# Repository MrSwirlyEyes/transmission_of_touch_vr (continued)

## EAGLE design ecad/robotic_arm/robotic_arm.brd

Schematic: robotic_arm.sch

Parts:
A6: 2.45GHz; ANTC6522X100
AVR_ISP: AVR ISP; HDRV6W64P254_2X3_762X508X838B
B1: 50/100; RESCAXE65P200X125X95-6
C1, C2, C3, C4, C5, C6, C7, C10, C12, C14, C16, C19, C22, C24, C26, C28, C30, C47, C48, C49, C50, C51, C52, C53, C54, C63, C79, C83, C85, C93, C96, C98: 0.1uF/50V; CAPC1005X55_SMD-0402
C8, C29, C92: 10uF/6.3V; CAPC1005X55_SMD-0402
C9, C11, C13, C15, C17: 100uF/25V; CAPPRD200W50D500H1100B
C20, C27, C80: 1000uF/16V; CAPPRD350W60D800H2000B
C21, C23, C55, C57, C58: 1uF/25V; CAPC1005X55_SMD-0402
C59, C60: 12pF/100V; CAPC1005X55_SMD-0402
C61: 22pF/100V/0402; CAPC1005X55_SMD-0402
C62: 0.75pF/50V; CAPC1005X55_SMD-0402
C94, C95, C97: 10uF/25V; CAPC2012X95_SMD-0805
D1: 150mA/75V; DFN100X60X55-2
D2, D7: 1A/50V; SODFL3516X170
DEMUX1: CH16_MUX-DEMUX; SOP65P780X200-24
FSR_INDEX: 10K; _MOLEX-0530470210_VERT_PITCH-1.25MM
FSR_MIDDLE: 10K; _MOLEX-0530470210_VERT_PITCH-1.25MM
FSR_PALM: 10K; _MOLEX-0530470210_VERT_PITCH-1.25MM
FSR_PINKY: 10K; _MOLEX-0530470210_VERT_PITCH-1.25MM
FSR_RING: 10K; _MOLEX-0530470210_VERT_PITCH-1.25MM
FSR_THUMB: 10K; _MOLEX-0530470210_VERT_PITCH-1.25MM
J1: 5A/28V; POWER_JACK_PTH_ID2.1MM-OD5.5MM
JP1: PTH RA VERT MALE; HDRRA6W64P254_1X6_1524X254X254B_FTDI
JP3: JUMPER_SMD_3-PAD_NO_SILK; SMT-JUMPER_3_NO_SILK
L1, L2: 10uH/380mA; INDC1608X60-0603
LED1: BLUE; LEDC1005X40_LED-0402
LIPO1: LIPO 2S; 1X02_WIRE_CONNECTOR_AWG-18
MCU: ATMEGA128RFA1; QFN50P900X900X90-64
NOISE_BR, NOISE_BR1: NET_BRIDGE
PWM_DRIVER: PCA9685; SOP65P650X110-28
R1, R10, R16, R39, R40, R41, R42, R43: 10K; RESC1005X35_SMD-0402
R2, R3: 1K; RESC1005X35_SMD-0402
R17, R18: 4.7K; RESC1005X35_SMD-0402
RX_LED: RED; LEDC1005X40_LED-0402
SERVO_INDEX: HK15298B; HDRV3W64P254_1X3_762X254X838B
SERVO_MIDDLE: HK15298B; HDRV3W64P254_1X3_762X254X838B
SERVO_PINKY: HK15298B; HDRV3W64P254_1X3_762X254X838B
SERVO_RING: HK15298B; HDRV3W64P254_1X3_762X254X838B
SERVO_THUMB: HK15298B; HDRV3W64P254_1X3_762X254X838B
SW1: 5A/28V; SW_TOGGLE_SPDT_5A-28V_13L-7W
TEMP_INDEX: TMP36; _MOLEX-0530470310_VERT_PITCH-1.25MM
TEMP_MIDDLE: TMP36; _MOLEX-0530470310_VERT_PITCH-1.25MM
TEMP_PINKY: TMP36; _MOLEX-0530470310_VERT_PITCH-1.25MM
TEMP_RING: TMP36; _MOLEX-0530470310_VERT_PITCH-1.25MM
TEMP_THUMB: TMP36; _MOLEX-0530470310_VERT_PITCH-1.25MM
TX_LED: GREEN; LEDC1005X40_LED-0402
VREG-ANALOG: MCP1700-1802 1.8V/200mA; SOT95P237X112-3_SOT-23-3
VREG-MCU: TPS76833QDR 1A/3.3V; SOIC127P600X265-8
VREG-SERVOS: MIC29501-5.0 5A/5V; TO170P1363X457-6
Y1: 16 MHz; OSCCC500X320X110_CRYSTAL

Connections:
3.3V: C19.1, C24.1, C52.1, C53.1, C54.1, C55.1, C58.1, C63.1, C92.1, C93.1, D1.K, D2.A, L1.1, MCU.23 (DEVDD), MCU.34 (DEVDD), MCU.44 (DEVDD), MCU.54 (DEVDD), PWM_DRIVER.28 (VCC), R17.2, R18.2, R43.2, VREG-MCU.5 (VOUT), VREG-MCU.6 (VOUT)
5V: C1.1, C9.A, C10.1, C11.A, C12.1, C13.A, C14.1, C15.A, C16.1, C17.A, C20.A, C83.1, C94.1, D7.A, SERVO_INDEX.VCC, SERVO_MIDDLE.VCC, SERVO_PINKY.VCC, SERVO_RING.VCC, SERVO_THUMB.VCC, VREG-SERVOS.4 (VOUT)
+: J1.PWR, LIPO1.+, SW1.S1
-: J1.GND_BATTERY, LIPO1.-
A1.8V: C28.1, C29.1, JP3.1, MCU.62 (AREF), VREG-ANALOG.2 (VO)
A3.3V: C2.1, C3.1, C4.1, C5.1, C6.1, C7.1, C8.1, C22.1, C23.1, C26.1, C85.1, DEMUX1.24 (VCC), JP3.3, L1.2, MCU.59 (EVDD), TEMP_INDEX.VCC, TEMP_MIDDLE.VCC, TEMP_PINKY.VCC, TEMP_RING.VCC, TEMP_THUMB.VCC, VREG-ANALOG.3 (VI)
AGND: B1.5 (GND), C2.2, C3.2, C4.2, C5.2, C6.2, C7.2, C8.2, C22.2, C23.2, C24.2, C26.2, C28.2, C29.2, C30.2, C47.2, C48.2, C49.2, C50.2, C51.2, C61.2, C62.2, C85.2, DEMUX1.2 (C7), DEMUX1.3 (C6), DEMUX1.12 (GND), DEMUX1.15 (!EN), DEMUX1.21 (C10), DEMUX1.22 (C9), DEMUX1.23 (C8), L2.2, MCU.7 (AVSS_RFP), MCU.10 (AVSS_RFN), MCU.58 (AVSS), MCU.61 (AVSS), MCU.EP (AVSS), MCU.P$1 (AVSS), MCU.P$2 (AVSS), MCU.P$3 (AVSS), MCU.P$4 (AVSS), MCU.P$5 (AVSS), R10.1, R16.1, R39.1, R40.1, R41.1, R42.1, TEMP_INDEX.GND, TEMP_MIDDLE.GND, TEMP_PINKY.GND, TEMP_RING.GND, TEMP_THUMB.GND, VREG-ANALOG.1 (GND)
FSR_INDEX: DEMUX1.8 (C1), FSR_INDEX.2 (-), R39.2
FSR_MIDDLE: DEMUX1.7 (C2), FSR_MIDDLE.2 (-), R40.2
FSR_PALM: DEMUX1.4 (C5), FSR_PALM.2 (-), R10.2
FSR_PINKY: DEMUX1.5 (C4), FSR_PINKY.2 (-), R42.2
FSR_RING: DEMUX1.6 (C3), FSR_RING.2 (-), R41.2
FSR_THUMB: DEMUX1.9 (C0), FSR_THUMB.2 (-), R16.2
GND: AVR_ISP.GND, C19.2, C21.2, C27.K, C52.2, C53.2, C54.2, C55.2, C57.2, C58.2, C59.1, C60.1, C63.2, C80.K, C92.2, C93.2, C95.2, C96.2, J1.GND_JACK, JP1.GND, MCU.11 (TST), MCU.20 (DVSS), MCU.24 (DVSS), MCU.33 (CLKI), MCU.35 (DVSS), MCU.45 (DVSS), MCU.55 (DVSS), NOISE_BR.P$2, NOISE_BR1.P$1, PWM_DRIVER.1 (A0), PWM_DRIVER.2 (A1), PWM_DRIVER.3 (A2), PWM_DRIVER.4 (A3), PWM_DRIVER.5 (A4), PWM_DRIVER.14 (GND), PWM_DRIVER.23 (!OE), PWM_DRIVER.24 (A5), PWM_DRIVER.25 (EXTCLK), R1.1, R2.1, R3.1, VREG-MCU.1 (GND), VREG-MCU.2 (!EN)
MISO: AVR_ISP.MISO, MCU.39 ((PDO/PCINT3/MISO/D12)PB3)
MOSI: AVR_ISP.MOSI, MCU.38 ((PDI/PCINT2/MOSI/D11)PB2)
unnamed: L2.1, NOISE_BR1.P$2
unnamed: LED1.K, R1.2
unnamed: R3.2, TX_LED.K
unnamed: R2.2, RX_LED.K
unnamed: C21.1, MCU.21 (DVDD), MCU.22 (DVDD)
unnamed: C57.1, MCU.60 (AVDD)
unnamed: C60.2, MCU.57 (XTAL1), Y1.1 (XTAL1)
unnamed: B1.3 (OUT1), MCU.9 (RFN)
unnamed: B1.4 (OUT2), MCU.8 (RFP)
unnamed: B1.2 (GND), C61.1
unnamed: C59.2, MCU.56 (XTAL2), Y1.3 (XTAL2)
unnamed: A6.1, B1.1 (IN), C62.1
unnamed: C79.1, JP1.DTR
NGND: C1.2, C9.K, C10.2, C11.K, C12.2, C13.K, C14.2, C15.K, C16.2, C17.K, C20.K, C83.2, C94.2, C97.2, C98.2, NOISE_BR.P$1, SERVO_INDEX.GND, SERVO_MIDDLE.GND, SERVO_PINKY.GND, SERVO_RING.GND, SERVO_THUMB.GND, VREG-SERVOS.3 (GND), VREG-SERVOS.TAB (GND)
RESET: AVR_ISP.RESET, C79.2, D1.A, MCU.12 (RSTN), R43.1
RX: JP1.TXO, MCU.46 ((PCINT8/RXD0/D0)PE0)
RX_LED: MCU.42 ((PCINT6/OC1B/D34-PWM34)PB6), RX_LED.A
S0: DEMUX1.10 (S0), MCU.50 ((INT4/OC3B/D4-PWM4)PE4)
S1: DEMUX1.11 (S1), MCU.49 ((AIN1/OC3A/D3-PWM3)PE3)
S2: DEMUX1.14 (S2), MCU.52 ((T3/INT6/D6)PE6)
S3: DEMUX1.13 (S3), MCU.51 ((INT5/OC3C/D5-PWM5)PE5)
SCK: AVR_ISP.SCK, MCU.37 ((PCINT1/SCK/D13)PB1)
SCL: MCU.25 ((INT0/SCL/D15)PD0), PWM_DRIVER.26 (SCL), R17.1
SDA: MCU.26 ((INT1/SDA/D14)PD1), PWM_DRIVER.27 (SDA), R18.1
SERVO_INDEX: PWM_DRIVER.18 (PWM11), SERVO_INDEX.SIG
SERVO_MIDDLE: PWM_DRIVER.17 (PWM10), SERVO_MIDDLE.SIG
SERVO_PINKY: PWM_DRIVER.15 (PWM8), SERVO_PINKY.SIG
SERVO_RING: PWM_DRIVER.16 (PWM9), SERVO_RING.SIG
SERVO_THUMB: PWM_DRIVER.19 (PWM12), SERVO_THUMB.SIG
SIG: DEMUX1.1 (SIG), MCU.1 ((ADC2/DIG2/A2*)PF2)
TEMP_INDEX: DEMUX1.17 (C14), TEMP_INDEX.SIG
TEMP_MIDDLE: DEMUX1.18 (C13), TEMP_MIDDLE.SIG
TEMP_PINKY: DEMUX1.20 (C11), TEMP_PINKY.SIG
TEMP_RING: DEMUX1.19 (C12), TEMP_RING.SIG
TEMP_THUMB: DEMUX1.16 (C15), TEMP_THUMB.SIG
TX: JP1.RXI, MCU.47 ((TXD0/D1)PE1)
TX_LED: MCU.43 ((PCINT7/OC0A/OC1C/D35-PWM35)PB7), TX_LED.A
VBAT: C27.A, C80.A, C95.1, C96.1, C97.1, C98.1, D2.K, D7.K, LED1.A, SW1.P, VREG-MCU.3 (VIN), VREG-MCU.4 (VIN), VREG-SERVOS.1 (EN), VREG-SERVOS.2 (VIN)
VSENSOR: C30.1, C47.1, C48.1, C49.1, C50.1, C51.1, FSR_INDEX.1 (+), FSR_MIDDLE.1 (+), FSR_PALM.1 (+), FSR_PINKY.1 (+), FSR_RING.1 (+), FSR_THUMB.1 (+), JP3.2

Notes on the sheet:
TEMP SENSORS
NOTE: Value depends on sensitivity
SERVOS
ANALOG DEMUX
PWM DRIVER
FORCE SENSITIVE RESISTORS
Might add op amps
ATMEGA128RFA1
ACTUATORS
SENSORS
AVR ISP
FTDI
PROGRAMMER
POWER SYSTEM
MCU
LPF
TRANSMISSION OF TOUCH VR
ROBOTIC ARM
Rev 3

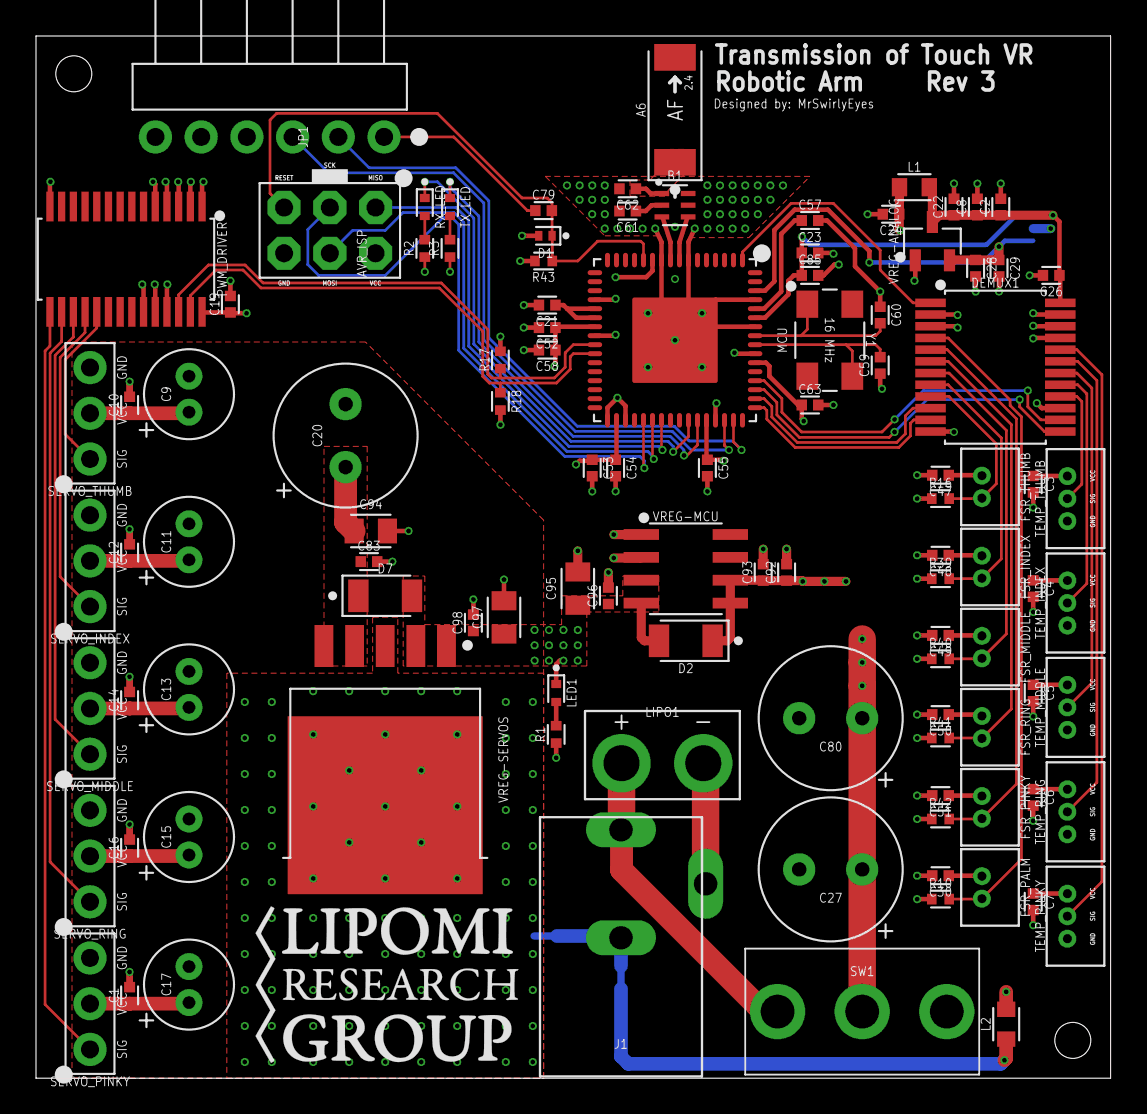
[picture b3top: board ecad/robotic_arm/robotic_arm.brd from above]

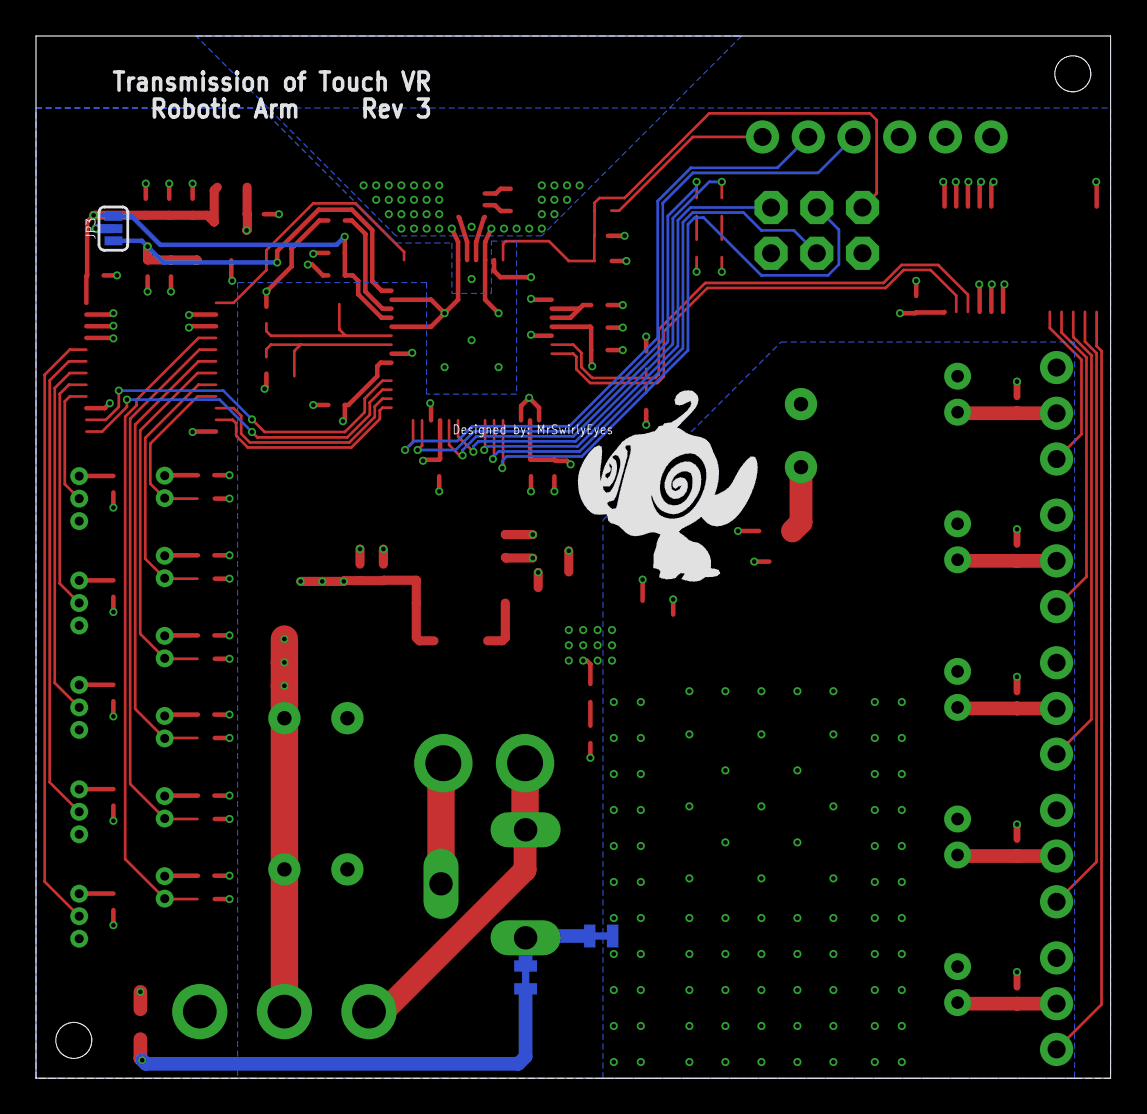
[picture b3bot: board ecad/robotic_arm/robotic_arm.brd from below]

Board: 4 copper layers, 59.7 x 57.9 mm, 112 parts (4 on the bottom side), 55 nets.

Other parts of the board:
U$17, U$18: HOLE_2MM
U$20: MRSWIRLYEYES-LOGO
U$21: LRG-LOGO

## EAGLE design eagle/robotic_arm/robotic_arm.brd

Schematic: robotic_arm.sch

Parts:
A6: 2.4GHz/802.11/0.5dBi/3W; ANTENNA-CHIP5
ANALOG_BR: 2PT_GND_TIE
AVR_ISP: AVR ISP; 2X3-NS
B1: Impedence UNBAL/BAL (50Ω/100Ω); 0805_BALUN
BATT1: BATTERYPTH_HOLES; DUAL_PTH_PADS
C1, C3, C4, C5, C6, C7, C8, C10, C12, C14, C16, C19, C22, C26, C47, C48, C49, C50, C51, C52, C54, C63, C79, C81, C83, C85, C93, C96, C98: 0.1uF/50V; _CER_SMD-805
C2, C9, C11, C13, C15, C17: 10uF/20V; _TANT_SMD-1206
C18, C25, C82, C92, C94, C95, C97: 10uF/25V; _CER_SMD-805
C20: 100UF/16V; _AE_SMD_L6.6-W6.6
C21, C23, C24, C53, C55, C57, C58: 1uF/25V; _CER_SMD-805
C59, C60: 12pF/250V; _CER_SMD-805
C61: 22PF/250V; _CER_SMD-805
C62: 0.75PF/100V; _CER_SMD-805
C80: 220uF/16V; _AE_SMD_L6.6-W6.6
D1, D6, D7: 1A/50V; SOD123F
DEMUX1: CH16_MUX-DEMUX; SSOP-24
FSR_INDEX: FSR; CONNECTOR_FSR
FSR_MIDDLE: FSR; CONNECTOR_FSR
FSR_PINKY: FSR; CONNECTOR_FSR
FSR_RING: FSR; CONNECTOR_FSR
FSR_THUMB: FSR; CONNECTOR_FSR
J1: (ID,OD)=(2.1,5.5)MM; POWER_JACK_SLOT_ID2.1MM-OD5.5MM
JP1: FTDIPTH-RA; FTDI_BASIC-6PIN-MALE-RA
L1, L2: 10uH; _SMD-805
L3: BLUE; LED_SMD-805_
L4: GREEN; LED_SMD-805_
L5: RED; LED_SMD-805_
MCU: ATMEGA128RFA1; VFQFN-64
NOISE_BR: 2PT_GND_TIE
PWM_DRIVER: PCA9685; TSSOP-28
R1, R4, R6, R8, R10, R12, R14, R16, R39, R40, R41, R42, R43: 10KΩ; RESISTOR_SMD-805
R2: 2KΩ; RESISTOR_SMD-805
R3: 1KΩ; RESISTOR_SMD-805
R5, R7, R9, R11, R13, R15: 100Ω; RESISTOR_SMD-805
R17, R18: 4.7K; RESISTOR_SMD-805
S7: TACTILE-SW_500mA/12V; BTN_MOMENTARY_SPST-NO_SMD_12V_50MA_L5.2-W5.2
SERVO_INDEX: HK15298B; CONNECTOR_SERVO
SERVO_MIDDLE: HK15298B; CONNECTOR_SERVO
SERVO_PINKY: HK15298B; CONNECTOR_SERVO
SERVO_RING: HK15298B; CONNECTOR_SERVO
SERVO_THUMB: HK15298B; CONNECTOR_SERVO
SERVO_WRIST: HK15298B; CONNECTOR_SERVO
SW1: 5A/28V; SW_TOGGLE_SPDT_5A-28V_13L-7W
TEMP_INDEX: TMP36; CONNECTOR_TMP36
TEMP_MIDDLE: TMP36; CONNECTOR_TMP36
TEMP_PINKY: TMP36; CONNECTOR_TMP36
TEMP_RING: TMP36; CONNECTOR_TMP36
TEMP_THUMB: TMP36; CONNECTOR_TMP36
VREG1: 5A/5V; TO-263-5
VREG3: 1A/3.3V; SOIC-8_W3.9MM
Y1: 16MHz; CRYSTAL-SMD-5X3

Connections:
5V: C1.1, C2.+ (A), C8.1, C9.+ (A), C10.1, C11.+ (A), C12.1, C13.+ (A), C14.1, C15.+ (A), C16.1, C17.+ (A), C20.A, C83.1, C94.1, D7.A, SERVO_INDEX.2 (VCC), SERVO_MIDDLE.2 (VCC), SERVO_PINKY.2 (VCC), SERVO_RING.2 (VCC), SERVO_THUMB.2 (VCC), SERVO_WRIST.2 (VCC), VREG1.4 (VOUT)
A0: MCU.63 ((ADC0/A0*)PF0)
A1: MCU.64 ((ADC1/A1*)PF1)
A2: MCU.1 ((ADC2/DIG2/A2*)PF2)
A3: MCU.2 ((ADC3/DIG4/A3*)PF3)
A4: MCU.3 ((ADC4/TCK/A4*)PF4)
A5: DEMUX1.1 (SIG), MCU.4 ((ADC5/TMS/A5*)PF5)
A6: MCU.5 ((ADC6/TDO/A6*)PF6)
A7: MCU.6 ((ADC7/TDI/A7*)PF7)
AGND: ANALOG_BR.P$2, C3.2, C4.2, C5.2, C6.2, C7.2, C18.2, C22.2, C23.2, C24.2, C26.2, C47.2, C48.2, C49.2, C50.2, C51.2, C85.2, DEMUX1.12 (GND), DEMUX1.15 (!EN), MCU.58 (AVSS), MCU.61 (AVSS), R16.1, R39.1, R40.1, R41.1, R42.1, TEMP_INDEX.3 (GND), TEMP_MIDDLE.3 (GND), TEMP_PINKY.3 (GND), TEMP_RING.3 (GND), TEMP_THUMB.3 (GND)
AVCC: C3.1, C4.1, C5.1, C6.1, C7.1, C18.1, C22.1, C23.1, C24.1, C26.1, C47.1, C48.1, C49.1, C50.1, C51.1, C85.1, DEMUX1.24 (VCC), FSR_INDEX.+, FSR_MIDDLE.+, FSR_PINKY.+, FSR_RING.+, FSR_THUMB.+, L1.2, MCU.59 (EVDD), MCU.62 (AREF), TEMP_INDEX.1 (VS), TEMP_MIDDLE.1 (VS), TEMP_PINKY.1 (VS), TEMP_RING.1 (VS), TEMP_THUMB.1 (VS)
BATT_+: BATT1.+, J1.PWR, SW1.2
BATT_-: BATT1.- (N), J1.GND@2 (GND)
C5: DEMUX1.4 (C5)
C6: DEMUX1.3 (C6)
C7: DEMUX1.2 (C7)
C8: DEMUX1.23 (C8)
C9: DEMUX1.22 (C9)
C10: DEMUX1.21 (C10)
FSR_INDEX: DEMUX1.6 (C3), FSR_RING.-, R39.2
FSR_MIDDLE: DEMUX1.7 (C2), FSR_MIDDLE.-, R40.2
FSR_PINKY: DEMUX1.9 (C0), FSR_THUMB.-, R42.2
FSR_RING: DEMUX1.8 (C1), FSR_INDEX.-, R41.2
FSR_THUMB: DEMUX1.5 (C4), FSR_PINKY.-, R16.2
GND: AVR_ISP.6, B1.5 (GND), C19.2, C21.2, C25.2, C52.2, C53.2, C54.2, C55.2, C57.2, C58.2, C59.2, C60.2, C61.2, C62.2, C63.2, C80.K, C81.2, C82.2, C92.2, C93.2, C95.2, C96.2, J1.GND@1 (GND), JP1.GND (6), L2.1, MCU.7 (AVSS_RFP), MCU.10 (AVSS_RFN), MCU.11 (TST), MCU.20 (DVSS), MCU.24 (DVSS), MCU.33 (CLKI), MCU.35 (DVSS), MCU.45 (DVSS), MCU.55 (DVSS), NOISE_BR.P$2, PWM_DRIVER.1 (A0), PWM_DRIVER.2 (A1), PWM_DRIVER.3 (A2), PWM_DRIVER.4 (A3), PWM_DRIVER.5 (A4), PWM_DRIVER.14 (GND), PWM_DRIVER.23 (!OE), PWM_DRIVER.24 (A5), PWM_DRIVER.25 (EXTCLK), R1.1, R2.1, R3.1, R4.1, R6.1, R8.1, R10.1, R12.1, R14.1, S7.1, VREG3.1 (GND), VREG3.2 (!EN)
MISO: AVR_ISP.1, MCU.39 ((PDO/PCINT3/MISO/D12)PB3)
MOSI: AVR_ISP.4, MCU.38 ((PDI/PCINT2/MOSI/D11)PB2)
unnamed: R11.1, SERVO_WRIST.1 (SIG)
unnamed: L3.K, R1.2
unnamed: L4.K, R3.2
unnamed: R9.1, SERVO_THUMB.1 (SIG)
unnamed: L5.K, R2.2
unnamed: R7.1, SERVO_INDEX.1 (SIG)
unnamed: R5.1, SERVO_MIDDLE.1 (SIG)
unnamed: R15.1, SERVO_RING.1 (SIG)
unnamed: R13.1, SERVO_PINKY.1 (SIG)
unnamed: C21.1, MCU.21 (DVDD), MCU.22 (DVDD)
unnamed: C57.1, MCU.60 (AVDD)
unnamed: C60.1, MCU.57 (XTAL1), Y1.3 (2)
unnamed: B1.3 (OUT2), MCU.9 (RFN)
unnamed: B1.4 (OUT1), MCU.8 (RFP)
unnamed: B1.2 (GND), C61.1
unnamed: C59.1, MCU.56 (XTAL2), Y1.1
unnamed: ANALOG_BR.P$1, L2.2
unnamed: A6.FEED, B1.1 (IN), C62.1
unnamed: C79.1, JP1.DTR (2)
NGND: C1.2, C2.- (K), C8.2, C9.- (K), C10.2, C11.- (K), C12.2, C13.- (K), C14.2, C15.- (K), C16.2, C17.- (K), C20.K, C83.2, C94.2, C97.2, C98.2, NOISE_BR.P$1, SERVO_INDEX.3 (GND), SERVO_MIDDLE.3 (GND), SERVO_PINKY.3 (GND), SERVO_RING.3 (GND), SERVO_THUMB.3 (GND), SERVO_WRIST.3 (GND), VREG1.3 (GND), VREG1.TAB (GND)
PB4: MCU.40 ((PCINT4/OC2A/D9-PWM9)PB4)
PB5: MCU.41 ((PCINT5/OC1A/D8-PWM8)PB5)
PB6: L5.A, MCU.42 ((PCINT6/OC1B/D34-PWM34)PB6)
PB7: L4.A, MCU.43 ((PCINT7/OC0A/OC1C/D35-PWM35)PB7)
PD4: MCU.29 ((ICP1/D22)PD4)
PD5: MCU.30 ((XCK1/D23)PD5)
PD6: MCU.31 ((T1/D24)PD6)
PD7: MCU.32 ((T0/D25)PD7)
PE2: DEMUX1.10 (S0), MCU.48 ((XCK0/AIN0/D2)PE2)
PE3: MCU.49 ((AIN1/OC3A/D3-PWM3)PE3)
PE4: MCU.50 ((INT4/OC3B/D4-PWM4)PE4)
PE5: MCU.51 ((INT5/OC3C/D5-PWM5)PE5)
PE6: DEMUX1.11 (S1), MCU.52 ((T3/INT6/D6)PE6)
PE7: DEMUX1.14 (S2), MCU.53 ((ICP3/INT7/CLKO/D7)PE7)
PG0: MCU.14 ((DIG3/D16)PG0)
PG1: MCU.15 ((DIG1/D17)PG1)
PG2: MCU.16 ((AMR/D18)PG2)
PG3: MCU.17 ((TOSC2)PG3)
PG4: MCU.18 ((TOSC1)PG4)
PG5: MCU.19 ((OC0B/D19-PWM19)PG5)
PWM6: PWM_DRIVER.12 (PWM6)
PWM7: PWM_DRIVER.13 (PWM7)
PWM8: PWM_DRIVER.15 (PWM8)
PWM9: PWM_DRIVER.16 (PWM9)
PWM10: PWM_DRIVER.17 (PWM10)
PWM11: PWM_DRIVER.18 (PWM11)
PWM12: PWM_DRIVER.19 (PWM12)
PWM13: PWM_DRIVER.20 (PWM13)
PWM14: PWM_DRIVER.21 (PWM14)
PWM15: PWM_DRIVER.22 (PWM15)
RESET: AVR_ISP.5, C79.2, D1.A, MCU.12 (RSTN), R43.1, S7.3 (2)
RX0: JP1.TXO (4), MCU.46 ((PCINT8/RXD0/D0)PE0)
RX1: MCU.27 ((INT2/RXD1/D20)PD2)
SCK: AVR_ISP.3, MCU.37 ((PCINT1/SCK/D13)PB1)
SCL: MCU.25 ((INT0/SCL/D15)PD0), PWM_DRIVER.26 (SCL), R17.1
SDA: MCU.26 ((INT1/SDA/D14)PD1), PWM_DRIVER.27 (SDA), R18.1
SERVO_INDEX: PWM_DRIVER.9 (PWM3), R6.2, R7.2
SERVO_MIDDLE: PWM_DRIVER.8 (PWM2), R4.2, R5.2
SERVO_PINKY: PWM_DRIVER.6 (PWM0), R12.2, R13.2
SERVO_RING: PWM_DRIVER.7 (PWM1), R14.2, R15.2
SERVO_THUMB: PWM_DRIVER.10 (PWM4), R8.2, R9.2
SERVO_WRIST: PWM_DRIVER.11 (PWM5), R10.2, R11.2
SSN: DEMUX1.13 (S3), MCU.36 ((PCINT0/SSN/D10)PB0)
TEMP_INDEX: DEMUX1.17 (C14), TEMP_RING.2 (VOUT)
TEMP_MIDDLE: DEMUX1.18 (C13), TEMP_MIDDLE.2 (VOUT)
TEMP_PINKY: DEMUX1.20 (C11), TEMP_THUMB.2 (VOUT)
TEMP_RING: DEMUX1.19 (C12), TEMP_INDEX.2 (VOUT)
TEMP_THUMB: DEMUX1.16 (C15), TEMP_PINKY.2 (VOUT)
TX0: JP1.RXI (3), MCU.47 ((TXD0/D1)PE1)
TX1: MCU.28 ((INT3/TXD1/D21)PD3)
VBATT: C80.A, C81.1, C82.1, C95.1, C96.1, C97.1, C98.1, D6.K, D7.K, L3.A, SW1.1, VREG1.1 (EN), VREG1.2 (VIN), VREG3.3 (VIN), VREG3.4 (VIN)
VCC: AVR_ISP.2, C19.1, C25.1, C52.1, C53.1, C54.1, C55.1, C58.1, C63.1, C92.1, C93.1, D1.K, D6.A, JP1.VCC (1), L1.1, MCU.23 (DEVDD), MCU.34 (DEVDD), MCU.44 (DEVDD), MCU.54 (DEVDD), PWM_DRIVER.28 (VCC), R17.2, R18.2, R43.2, VREG3.5 (VOUT), VREG3.6 (VOUT)

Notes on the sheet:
TEMP SENSORS
NOTE: Value depends on sensitivity
SERVOS
NEED TO FULLY DEFINE THE SERVO DEVICE
ANALOG DEMUX
PWM DRIVER
I2C ADDR: x40
47K?
FORCE SENSITIVE RESISTORS
Might add op amps
ATMEGA128RFA1
ACTUATORS
SENSORS
CHECK THESE FOR ACCURACY
AVR ISP
FTDI
PROGRAMMER
POWER SYSTEM
MCU
LPF
TRANSMISSION OF TOUCH VR
ROBOTIC ARM
Rev 1
add diode CD1206-S01575
TODO: LOTS OF VIAS
CHANGE TO 470 UF
D10
A0/0 --> SIG_PIN of DEMUX
D2 --> S0 of DEMUX
D6 --> S1 of DEMUX
D7 --> S2 of DEMUX
D10 --> S3 of DEMUX
NOTES: Add more spots for another vibe motor?

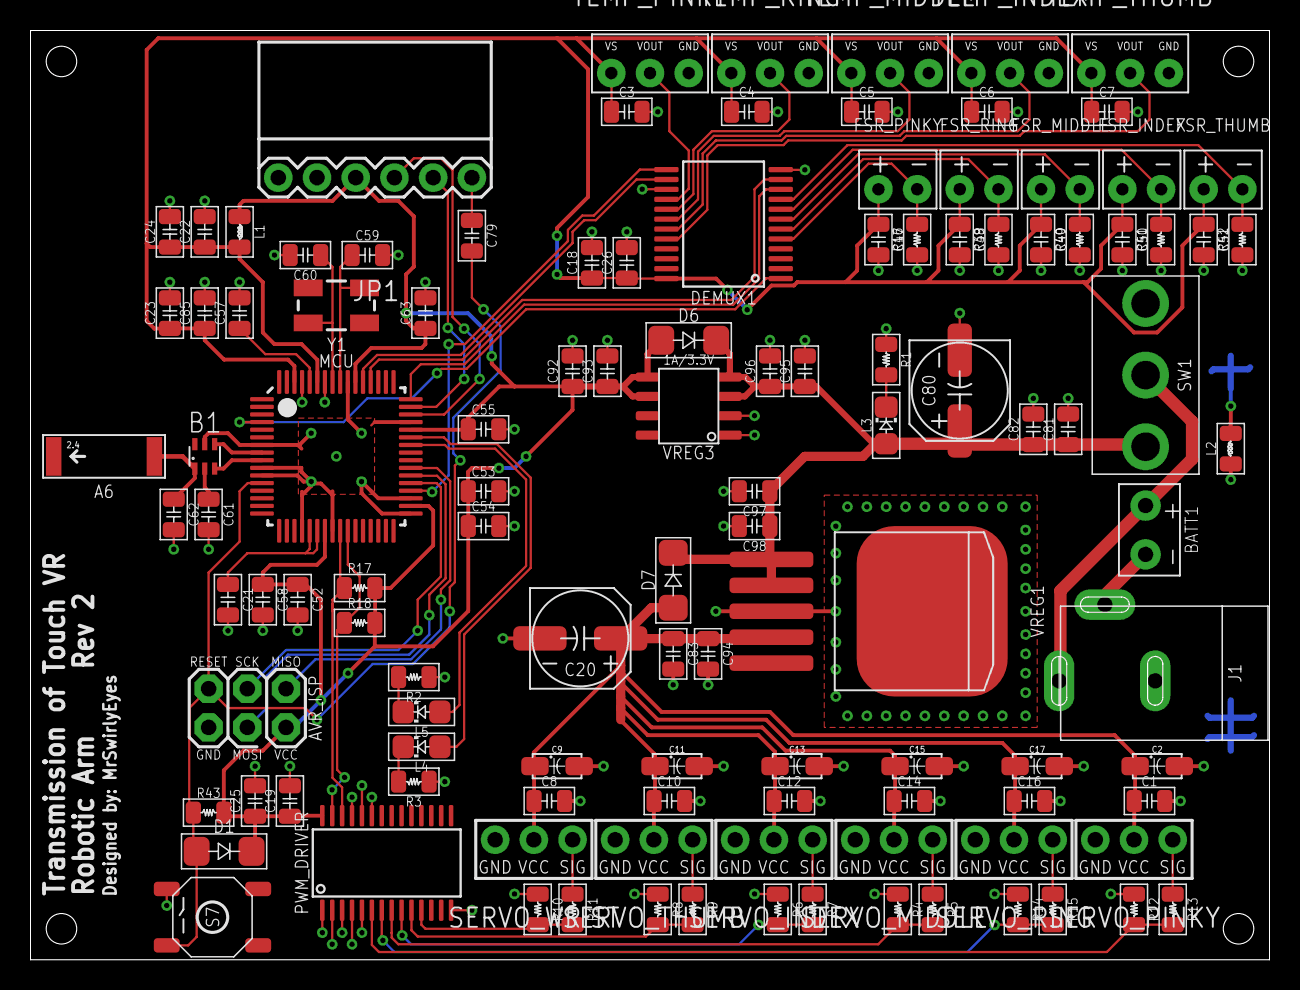
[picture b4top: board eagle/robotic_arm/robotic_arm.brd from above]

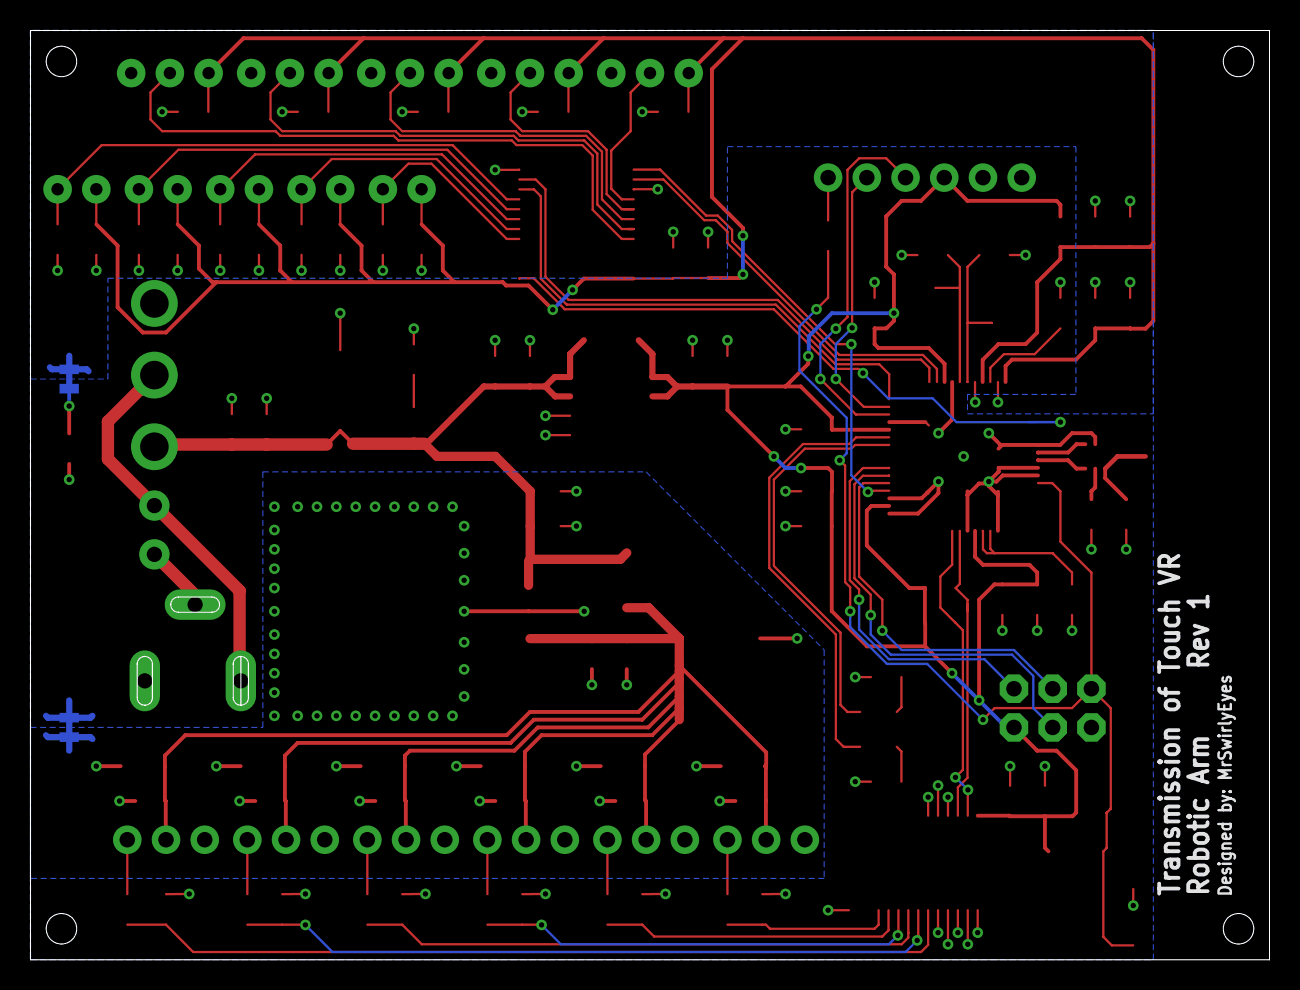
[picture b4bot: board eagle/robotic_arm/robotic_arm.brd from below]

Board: 2 copper layers, 81.3 x 61.0 mm, 118 parts (2 on the bottom side), 59 nets.

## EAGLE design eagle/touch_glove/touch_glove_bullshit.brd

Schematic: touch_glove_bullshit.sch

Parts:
A6: 2.4GHz/802.11/0.5dBi/3W; ANTENNA-CHIP5
ANALOG_BR: 2PT_GND_TIE
AVR_ISP: AVR ISP; 2X3-NS
B2: Impedence UNBAL/BAL (50Ω/100Ω); 0805_BALUN
BATT2: BATTERYPTH_HOLES; DUAL_PTH_PADS
C1, C3, C4, C5, C6, C7, C8, C9, C12, C13, C16, C17, C20, C21, C25, C26, C30, C31, C32, C33, C34, C36, C38, C40, C45, C47, C48, C49, C50, C51, C98, C100, C106, C108, C116, C117, C119, C122, C124, C127, C135: 0.1uF/50V; _CER_SMD_0402
C2, C42, C46, C118: 100uF/16V; _CER_SMD-1210
C10, C14, C18, C22, C27, C37, C39, C43, C44, C97, C99, C120, C123, C126: 10uF/10V; _CER_SMD_0402
C41: 47uF/10V; _CER_SMD-805
C107, C109, C110, C111, C132, C134, C136: 1uF/25V; _CER_SMD_0402
C112, C113: 12pF/100V; _CER_SMD_0402
C114: 22pF/50V; _CER_SMD_0402
C115: 0.75pF/50V; _CER_SMD_0402
D1, D2, D3, D4, D5, D11, D12: 150mA/75V; SOD-923F/0402
D8, D13, D14: 1A/50V; SOD123F
DEMUX1: CH16_MUX-DEMUX; SSOP-24
FLEX1, FLEX2, FLEX3, FLEX4, FLEX5, FLEX6, FLEX7, FLEX8, FLEX9, FLEX10: 10K; CONNECTOR_FSR
HBRIDGE1, HBRIDGE2, HBRIDGE3, HBRIDGE4, HBRIDGE5: DRV8837C; WSON-8-PPAD
JP2: FTDIPTH-RA; FTDI_BASIC-6PIN-MALE-RA
L3, L4: 10uH/0.38A; _SMD-0603
LED1: GREEN; LED_SMD-0402
LED2: RED; LED_SMD-0402
LED3: BLUE; LED_SMD-0402
MCU: ATMEGA128RFA1; VFQFN-64
NOISE_BR: 2PT_GND_TIE
PWM_DRIVER1: PCA9685; TSSOP-28
Q1, Q2, Q3, Q4, Q5, Q6: MCH3474 4A/30V/50mΩ; SC-70FL/MCPH3
R1, R2, R3, R4, R5, R12, R14, R16, R18, R20, R22, R24, R26, R28, R30, R32, R46, R47: 10KΩ; RESISTOR_SMD-0402
R6, R7, R8, R9, R10, R13, R15, R17, R19, R21, R23, R25, R27, R29, R31, R33: 100Ω; RESISTOR_SMD-0402
R11, R34, R35, R36, R37, R38, R39, R42, R43, R44: 47KΩ; RESISTOR_SMD-0402
R40, R41: 4.7KΩ; RESISTOR_SMD-0402
R48: 2KΩ; RESISTOR_SMD-0402
R49: 1KΩ; RESISTOR_SMD-0402
SW1: 4A/28V; SW_SLIDE_RA_SPDT_4A-28V_L12.7-W9.5
TEC1, TEC2, TEC3, TEC4, TEC5: PELTIER; CONNECTOR_PELTIER
VIBE1, VIBE2, VIBE3, VIBE4, VIBE5, VIBE6: VIBE_MOTOR; CONNECTOR_VIBE-MOTOR
VREG1: 1A/3.3V; SOIC-8_W3.9MM
VREG6: TL1963A-33 1.5A/3.3V; SOT223-4
VREG7: 3A/1.8V; DDPAK-5
Y2: 16MHz; CRYSTAL-SMD-5X3

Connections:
1.8V: C9.1, C10.1, C13.1, C14.1, C17.1, C18.1, C21.1, C22.1, C26.1, C27.1, C39.1, C40.1, C42.1, D14.A, HBRIDGE1.1 (VM), HBRIDGE2.1 (VM), HBRIDGE3.1 (VM), HBRIDGE4.1 (VM), HBRIDGE5.1 (VM), VREG7.4 (VOUT), VREG7.5 (SENSE)
3.3V: C1.1, C3.1, C4.1, C5.1, C6.1, C7.1, C36.1, C41.1, C43.1, D1.K, D2.K, D3.K, D4.K, D5.K, D12.K, D13.A, VIBE1.1 (+), VIBE2.1 (+), VIBE3.1 (+), VIBE4.1 (+), VIBE5.1 (+), VIBE6.1 (+), VREG6.3 (VO)
A0: MCU.63 ((ADC0/A0*)PF0)
A1: DEMUX1.1 (SIG), MCU.64 ((ADC1/A1*)PF1)
A2: MCU.1 ((ADC2/DIG2/A2*)PF2)
A3: MCU.2 ((ADC3/DIG4/A3*)PF3)
A4: MCU.3 ((ADC4/TCK/A4*)PF4)
A5: MCU.4 ((ADC5/TMS/A5*)PF5)
A6: MCU.5 ((ADC6/TDO/A6*)PF6)
A7: MCU.6 ((ADC7/TDI/A7*)PF7)
AGND: ANALOG_BR.P$2, C30.2, C31.2, C32.2, C33.2, C34.2, C47.2, C48.2, C49.2, C50.2, C51.2, C97.2, C100.2, C122.2, C134.2, C135.2, C136.2, DEMUX1.12 (GND), DEMUX1.15 (!EN), MCU.58 (AVSS), MCU.61 (AVSS), R11.1, R34.1, R35.1, R36.1, R37.1, R38.1, R39.1, R42.1, R43.1, R44.1
AVCC: C30.1, C31.1, C32.1, C33.1, C34.1, C47.1, C48.1, C49.1, C50.1, C51.1, C97.1, C100.1, C122.1, C134.1, C135.1, C136.1, DEMUX1.24 (VCC), FLEX1.+, FLEX2.+, FLEX3.+, FLEX4.+, FLEX5.+, FLEX6.+, FLEX7.+, FLEX8.+, FLEX9.+, FLEX10.+, L3.2, MCU.59 (EVDD), MCU.62 (AREF)
BATT_+: BATT2.+, SW1.P (1)
C8: DEMUX1.23 (C8)
C9: DEMUX1.22 (C9)
C10: DEMUX1.21 (C10)
C11: DEMUX1.20 (C11)
C12: DEMUX1.19 (C12)
C13: DEMUX1.18 (C13)
GND: AVR_ISP.6, B2.5 (GND), BATT2.- (N), C2.2, C8.2, C12.2, C16.2, C20.2, C25.2, C37.2, C38.2, C44.2, C45.2, C46.2, C98.2, C99.2, C106.2, C107.2, C108.2, C109.2, C110.2, C111.2, C112.2, C113.2, C114.2, C115.2, C116.2, C118.2, C119.2, C120.2, C123.2, C124.2, C126.2, C127.2, C132.2, JP2.GND (6), L4.1, MCU.7 (AVSS_RFP), MCU.10 (AVSS_RFN), MCU.11 (TST), MCU.20 (DVSS), MCU.24 (DVSS), MCU.33 (CLKI), MCU.35 (DVSS), MCU.45 (DVSS), MCU.55 (DVSS), NOISE_BR.P$2, PWM_DRIVER1.1 (A0), PWM_DRIVER1.2 (A1), PWM_DRIVER1.3 (A2), PWM_DRIVER1.4 (A3), PWM_DRIVER1.5 (A4), PWM_DRIVER1.14 (GND), PWM_DRIVER1.23 (!OE), PWM_DRIVER1.24 (A5), PWM_DRIVER1.25 (EXTCLK), R14.1, R16.1, R18.1, R20.1, R22.1, R24.1, R26.1, R28.1, R30.1, R32.1, R47.1, R48.1, R49.1, VREG1.1 (GND), VREG1.2 (!EN)
MISO: AVR_ISP.1, MCU.39 ((PDO/PCINT3/MISO/D12)PB3)
MOSI: AVR_ISP.4, MCU.38 ((PDI/PCINT2/MOSI/D11)PB2)
unnamed: HBRIDGE5.3 (OUT2), TEC5.HOT
unnamed: C6.2, D4.A, Q4.3 (D), VIBE4.2 (-)
unnamed: C7.2, D5.A, Q5.3 (D), VIBE5.2 (-)
unnamed: C5.2, D3.A, Q3.3 (D), VIBE3.2 (-)
unnamed: HBRIDGE5.2 (OUT1), TEC5.COLD
unnamed: HBRIDGE4.2 (OUT1), TEC4.COLD
unnamed: Q2.1 (G), R2.2, R7.2
unnamed: HBRIDGE4.5 (IN2), R14.2, R15.2
unnamed: Q3.1 (G), R3.2, R8.2
unnamed: HBRIDGE4.6 (IN1), R16.2, R17.2
unnamed: HBRIDGE4.3 (OUT2), TEC4.HOT
unnamed: HBRIDGE3.3 (OUT2), TEC3.HOT
unnamed: HBRIDGE3.5 (IN2), R18.2, R19.2
unnamed: HBRIDGE3.6 (IN1), R20.2, R21.2
unnamed: C4.2, D2.A, Q2.3 (D), VIBE2.2 (-)
unnamed: HBRIDGE3.2 (OUT1), TEC3.COLD
unnamed: C3.2, D1.A, Q1.3 (D), VIBE1.2 (-)
unnamed: HBRIDGE2.3 (OUT2), TEC2.HOT
unnamed: HBRIDGE2.5 (IN2), R22.2, R23.2
unnamed: HBRIDGE2.6 (IN1), R24.2, R25.2
unnamed: Q4.1 (G), R4.2, R9.2
unnamed: Q5.1 (G), R5.2, R10.2
unnamed: HBRIDGE2.2 (OUT1), TEC2.COLD
unnamed: HBRIDGE1.3 (OUT2), TEC1.HOT
unnamed: HBRIDGE1.5 (IN2), R26.2, R27.2
unnamed: HBRIDGE1.6 (IN1), R28.2, R29.2
unnamed: HBRIDGE1.2 (OUT1), TEC1.COLD
unnamed: Q1.1 (G), R1.2, R6.2
unnamed: HBRIDGE5.5 (IN2), R30.2, R31.2
unnamed: C1.2, D12.A, Q6.3 (D), VIBE6.2 (-)
unnamed: HBRIDGE5.6 (IN1), R32.2, R33.2
unnamed: Q6.1 (G), R12.2, R13.2
unnamed: C113.1, MCU.57 (XTAL1), Y2.3 (2)
unnamed: B2.3 (OUT2), MCU.9 (RFN)
unnamed: B2.4 (OUT1), MCU.8 (RFP)
unnamed: B2.2 (GND), C114.1
unnamed: C112.1, MCU.56 (XTAL2), Y2.1
unnamed: A6.FEED, B2.1 (IN), C115.1
unnamed: C117.1, JP2.DTR (2)
unnamed: ANALOG_BR.P$1, L4.2
unnamed: LED3.K, R47.2
unnamed: LED1.K, R49.2
unnamed: LED2.K, R48.2
unnamed: C132.1, MCU.21 (DVDD), MCU.22 (DVDD)
unnamed: C110.1, MCU.60 (AVDD)
NGND: C9.2, C10.2, C13.2, C14.2, C17.2, C18.2, C21.2, C22.2, C26.2, C27.2, C36.2, C39.2, C40.2, C41.2, C42.2, C43.2, HBRIDGE1.4 (GND), HBRIDGE1.GND, HBRIDGE1.P$1 (GND), HBRIDGE1.P$2 (GND), HBRIDGE2.4 (GND), HBRIDGE2.GND, HBRIDGE2.P$1 (GND), HBRIDGE2.P$2 (GND), HBRIDGE3.4 (GND), HBRIDGE3.GND, HBRIDGE3.P$1 (GND), HBRIDGE3.P$2 (GND), HBRIDGE4.4 (GND), HBRIDGE4.GND, HBRIDGE4.P$1 (GND), HBRIDGE4.P$2 (GND), HBRIDGE5.4 (GND), HBRIDGE5.GND, HBRIDGE5.P$1 (GND), HBRIDGE5.P$2 (GND), NOISE_BR.P$1, Q1.2 (S), Q2.2 (S), Q3.2 (S), Q4.2 (S), Q5.2 (S), Q6.2 (S), R1.1, R2.1, R3.1, R4.1, R5.1, R12.1, VREG6.2 (GND), VREG6.TAB (GND), VREG7.3 (GND), VREG7.TAB (GND)
PB4: MCU.40 ((PCINT4/OC2A/D9-PWM9)PB4)
PB5: MCU.41 ((PCINT5/OC1A/D8-PWM8)PB5)
PB6: LED2.A, MCU.42 ((PCINT6/OC1B/D34-PWM34)PB6)
PB7: LED1.A, MCU.43 ((PCINT7/OC0A/OC1C/D35-PWM35)PB7)
PD4: DEMUX1.13 (S3), MCU.29 ((ICP1/D22)PD4)
PD5: DEMUX1.14 (S2), MCU.30 ((XCK1/D23)PD5)
PD6: DEMUX1.11 (S1), MCU.31 ((T1/D24)PD6)
PD7: DEMUX1.10 (S0), MCU.32 ((T0/D25)PD7)
PE2: MCU.48 ((XCK0/AIN0/D2)PE2)
PE3: MCU.49 ((AIN1/OC3A/D3-PWM3)PE3)
PE4: MCU.50 ((INT4/OC3B/D4-PWM4)PE4)
PE5: MCU.51 ((INT5/OC3C/D5-PWM5)PE5)
PE6: MCU.52 ((T3/INT6/D6)PE6)
PE7: MCU.53 ((ICP3/INT7/CLKO/D7)PE7)
PG0: MCU.14 ((DIG3/D16)PG0)
PG1: MCU.15 ((DIG1/D17)PG1)
PG2: MCU.16 ((AMR/D18)PG2)
PG3: MCU.17 ((TOSC2)PG3)
PG4: MCU.18 ((TOSC1)PG4)
PG5: MCU.19 ((OC0B/D19-PWM19)PG5)
RESET: AVR_ISP.5, C117.2, D11.A, MCU.12 (RSTN), R46.1
RX0: JP2.TXO (4), MCU.46 ((PCINT8/RXD0/D0)PE0)
RX1: MCU.27 ((INT2/RXD1/D20)PD2)
SCK: AVR_ISP.3, MCU.37 ((PCINT1/SCK/D13)PB1)
SCL: MCU.25 ((INT0/SCL/D15)PD0), PWM_DRIVER1.26 (SCL), R40.1
SDA: MCU.26 ((INT1/SDA/D14)PD1), PWM_DRIVER1.27 (SDA), R41.1
SSN: MCU.36 ((PCINT0/SSN/D10)PB0)
STRAIN_1: DEMUX1.9 (C0), FLEX2.-, R34.2
STRAIN_2: DEMUX1.8 (C1), FLEX7.-, R39.2
STRAIN_3: DEMUX1.7 (C2), FLEX3.-, R35.2
STRAIN_4: DEMUX1.6 (C3), FLEX8.-, R42.2
STRAIN_5: DEMUX1.5 (C4), FLEX4.-, R36.2
STRAIN_6: DEMUX1.4 (C5), FLEX9.-, R43.2
STRAIN_7: DEMUX1.3 (C6), FLEX5.-, R37.2
STRAIN_8: DEMUX1.2 (C7), FLEX10.-, R44.2
STRAIN_9: DEMUX1.17 (C14), FLEX1.-, R11.2
STRAIN_10: DEMUX1.16 (C15), FLEX6.-, R38.2
TEC_1_COLD: PWM_DRIVER1.12 (PWM6), R27.1
TEC_1_HOT: PWM_DRIVER1.13 (PWM7), R29.1
TEC_2_COLD: PWM_DRIVER1.21 (PWM14), R23.1
TEC_2_HOT: PWM_DRIVER1.22 (PWM15), R25.1
TEC_3_COLD: PWM_DRIVER1.19 (PWM12), R19.1
TEC_3_HOT: PWM_DRIVER1.20 (PWM13), R21.1
TEC_4_COLD: PWM_DRIVER1.17 (PWM10), R15.1
TEC_4_HOT: PWM_DRIVER1.18 (PWM11), R17.1
TEC_5_COLD: PWM_DRIVER1.15 (PWM8), R31.1
TEC_5_HOT: PWM_DRIVER1.16 (PWM9), R33.1
TX0: JP2.RXI (3), MCU.47 ((TXD0/D1)PE1)
TX1: MCU.28 ((INT3/TXD1/D21)PD3)
VBATT: C2.1, C37.1, C38.1, C44.1, C45.1, C46.1, C118.1, C119.1, C120.1, C126.1, C127.1, D8.K, D13.K, D14.K, LED3.A, SW1.S1 (2), VREG1.3 (VIN), VREG1.4 (VIN), VREG6.1 (VI), VREG7.1 (!SHDN), VREG7.2 (VIN)
VCC: AVR_ISP.2, C8.1, C12.1, C16.1, C20.1, C25.1, C98.1, C99.1, C106.1, C107.1, C108.1, C109.1, C111.1, C116.1, C123.1, C124.1, D8.A, D11.K, HBRIDGE1.7 (NSLEEP), HBRIDGE1.8 (VCC), HBRIDGE2.7 (NSLEEP), HBRIDGE2.8 (VCC), HBRIDGE3.7 (NSLEEP), HBRIDGE3.8 (VCC), HBRIDGE4.7 (NSLEEP), HBRIDGE4.8 (VCC), HBRIDGE5.7 (NSLEEP), HBRIDGE5.8 (VCC), JP2.VCC (1), L3.1, MCU.23 (DEVDD), MCU.34 (DEVDD), MCU.44 (DEVDD), MCU.54 (DEVDD), PWM_DRIVER1.28 (VCC), R40.2, R41.2, R46.2, VREG1.5 (VOUT), VREG1.6 (VOUT)
VIBE_1: PWM_DRIVER1.6 (PWM0), R6.1
VIBE_2: PWM_DRIVER1.7 (PWM1), R7.1
VIBE_3: PWM_DRIVER1.8 (PWM2), R8.1
VIBE_4: PWM_DRIVER1.9 (PWM3), R9.1
VIBE_5: PWM_DRIVER1.10 (PWM4), R10.1
VIBE_6: PWM_DRIVER1.11 (PWM5), R13.1

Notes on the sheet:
VIBROTACTILE DRIVERS
PELTIER DRIVERS
47K?
FLEX SENSORS
Might add op amps
ANALOG DEMUX
PWM DRIVER
I2C ADDR: x40
ATMEGA128RFA1
ACTUATORS
SENSORS
CHECK THESE FOR ACCURACY
AVR ISP
FTDI
PROGRAMMER
POWER SYSTEM
MCU
LPF
TRANSMISSION OF TOUCH VR
ROBOTIC ARM
Rev 1
add diode CD1206-S01575
TODO: LOTS OF VIAS
D10
A0/0 --> SIG_PIN of DEMUX
D2 --> S0 of DEMUX
D6 --> S1 of DEMUX
D7 --> S2 of DEMUX
D10 --> S3 of DEMUX
VIBROTACTILES
THERMOELECTRICS
deleted reset SW
test
TRY to change these pins?
was PE2
was PE6
was PE7
was SSN

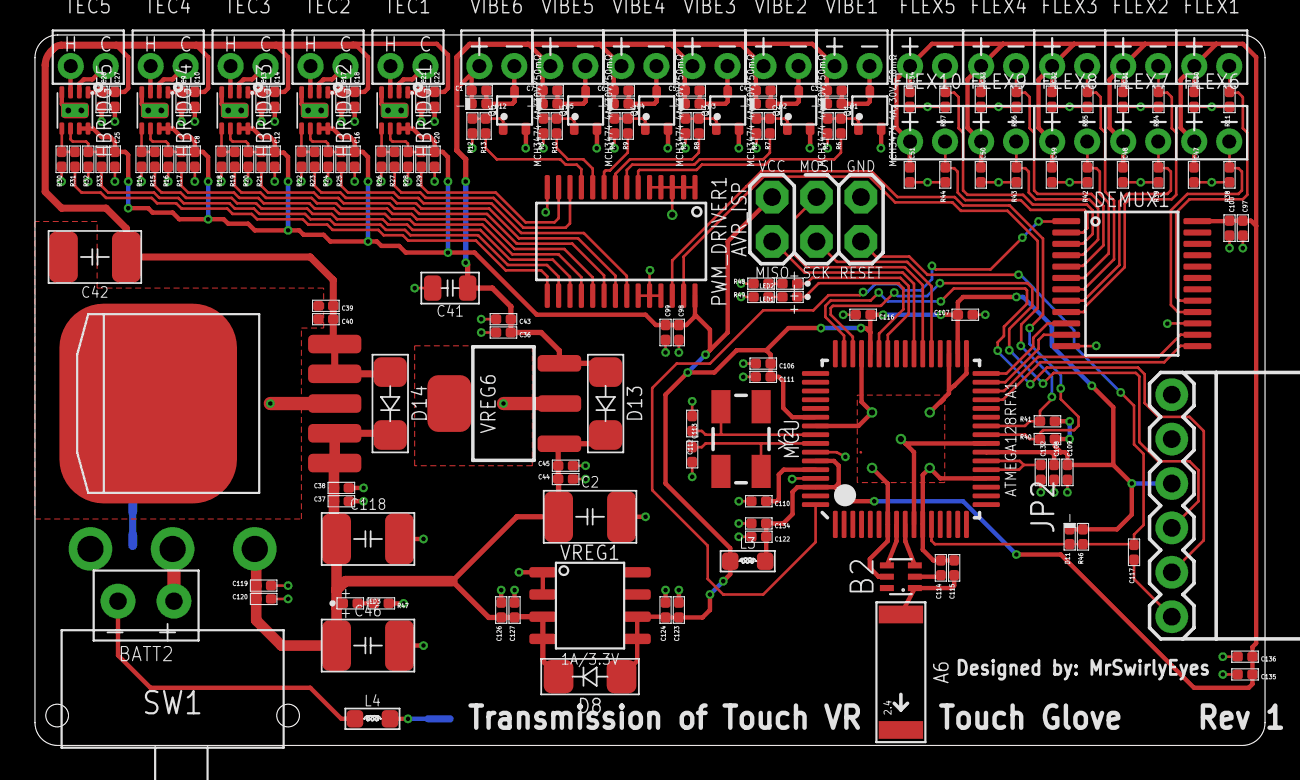
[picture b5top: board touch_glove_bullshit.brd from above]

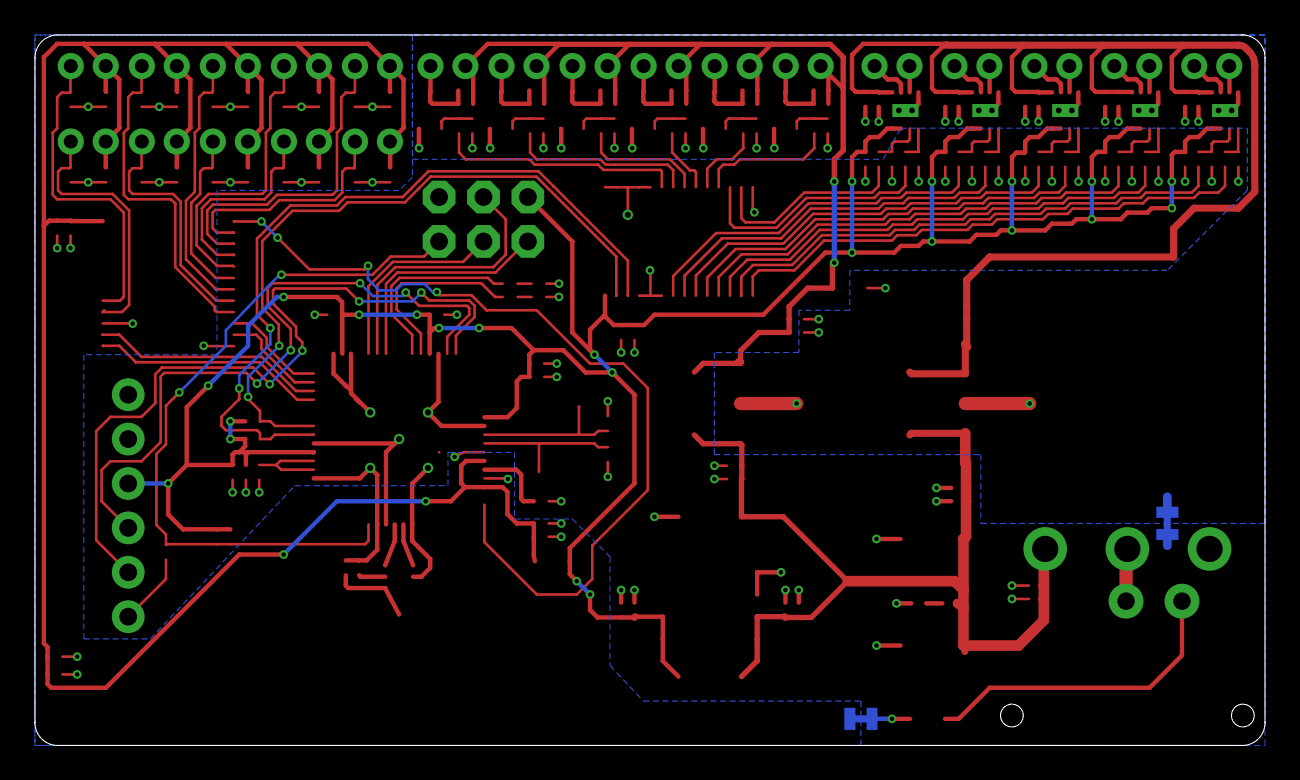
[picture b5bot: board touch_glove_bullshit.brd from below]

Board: 2 copper layers, 70.4 x 40.6 mm, 181 parts (2 on the bottom side), 95 nets.
